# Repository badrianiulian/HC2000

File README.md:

# HC2000

## Note în limba română
Proiect de reconstrucție HC2000

Ce s-a folosit pentru a crea acest proiect:
- Versiunea originală a schemei HC-2000 Rev B care a fost obținută prin intermediul grupului Romanian Home Computer (mulțumiri speciale domnului George Chirtoacă)
- Schema Eagle a HC-2000 Rev B realizată de dl. Liviu Grama, care este de asemenea membru al grupului Romanian Home Computer
- Un exemplar fizic al unui HC-2000 Rev E furnizat de dl. Oică Cezar pentru reparații

Note despre diferențe:
- HC2000_ORIGINAL este proiectul realizat folosind scanările cablajului exemplarului fizic HC-2000 Rev E
- gerberele au fost create folosind proiectul HC2000, care este Rev E modificată pentru a include firele lipite peste cablaj
- unde se întâlnește un "-", înseamnă că acea componentă lipsește pe cablajul Rev E, dar locul de amplasare al componentei este disponibil
- pentru conectorul de alimentare am adăugat pe lângă locul de amplasare al conectorului original, un conector cu 6 pini DIN

**IMPORTANT**: În prima revizie a proiectului s-au strecurat câteva greșeli:
- Nu am observat o tăietură pe placa originală ceea ce a dus la unirea a două trasee. Această secțiune este documentată pe grupul Romanian Home Computer de Radioman V: https://groups.google.com/g/romanianhomecomputer/c/qHbKBThCIQc/m/c_SBp--mCgAJ

- Au rămas două circuite cu titulatura veche de pe proiectul original care a fost convertit:

- Portul serial a fost testat de svpantazi. Modificarea se face sub UE10:

## English notes
HC2000 rebuild project

What was used to create this project:
- Original version of the schematic of HC-2000 Rev B that was obtained through the Romanian Home Computer group (special thanks to mr. George Chirtoacă)
- Eagle schematic of the HC-2000 Rev B made by mr. Liviu Grama also a member of the Romanian Home Computer group
- A physical HC-2000 Rev E provided by mr. Oică Cezar for repairs

Notes on the diferences:
- HC2000_ORIGINAL is the project made using PCB scans of the physical HC-2000 Rev E
- gerbers were created using HC2000 project witch is the modified Rev E witch includes the over-the-PCB soldered wires
- where a "-" is encountered, it means that the component is missing on Rev E but the footprint is available
- for the power connector I added side by side with the original connector's footprint, a 6-pin DIN connector

**IMPORTANT**: In the original project a few mistakes slipped in.
- I did not notice a cut on the original PCB witch led to joining of two tracks. This section is documented on the Romanian Home Computer group by Radioman V: https://groups.google.com/g/romanianhomecomputer/c/qHbKBThCIQc/m/c_SBp--mCgAJ

- Two circuits retained the old names from the original converted project:

- The serial port was tested by svpantazi. The fix is under UE10:

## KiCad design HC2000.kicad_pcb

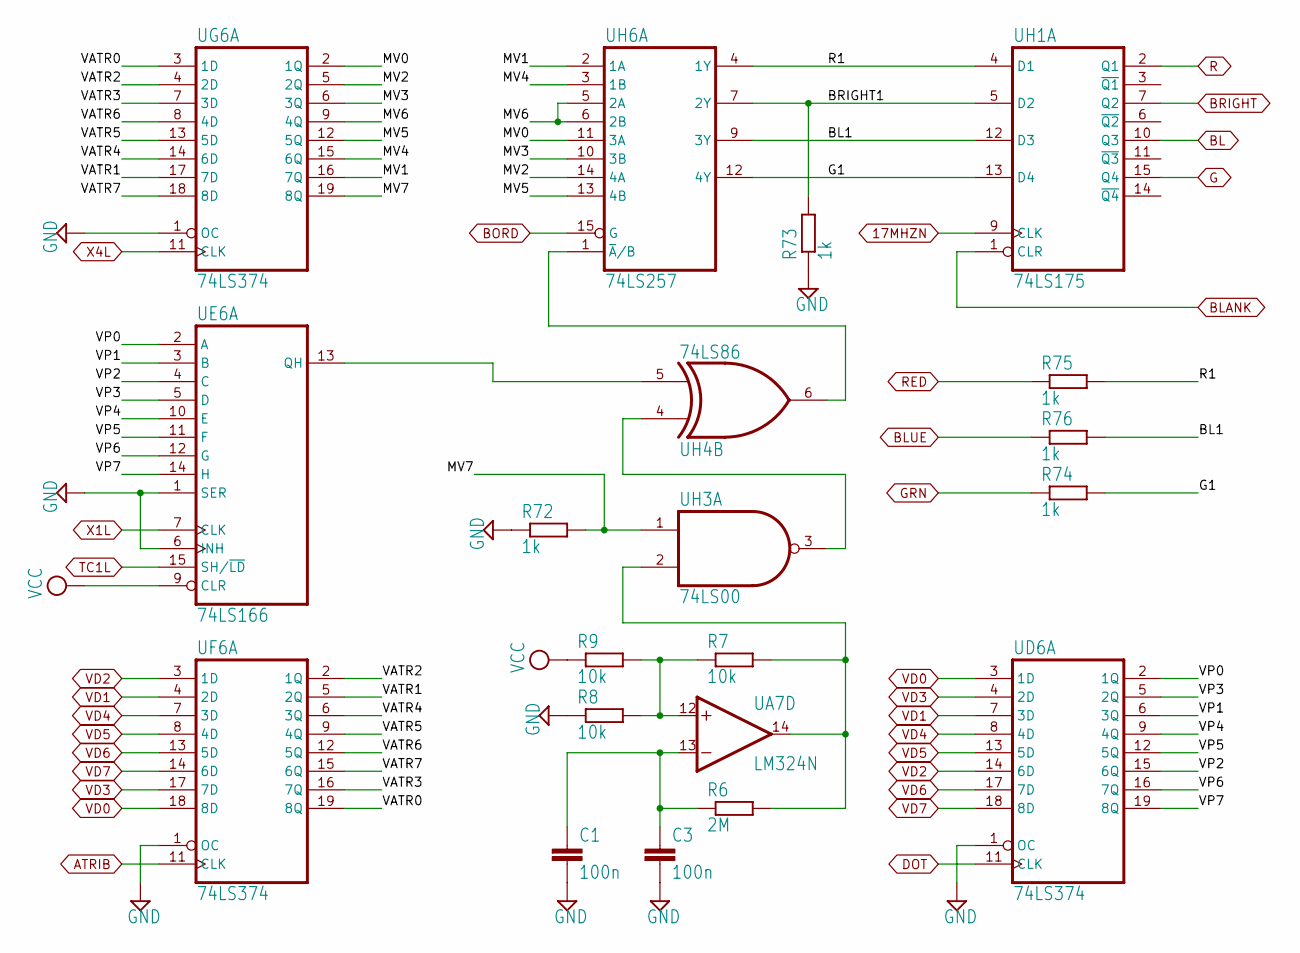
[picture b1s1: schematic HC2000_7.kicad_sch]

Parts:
C1, C3: 100n; C025-030X050
R6: 2M; 0204_7
R7, R8, R9: 10k; 0204_7
R72, R73, R74, R75, R76: 1k; 0204_7
UA7: LM324N; DIL14
UD6: 74LS374; DIL20
UE6: 74LS166; DIL16
UF6: 74LS374; DIL20
UG6: 74LS374; DIL20
UH1: 74LS175; DIL16
UH3: 74LS00; DIL14
UH4: 74LS86; DIL14
UH6: 74LS257; DIL16

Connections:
17MHZN: UH1.9 (CLK); also elsewhere on the board
/HC2000_7/BL1: R76.2, UH1.12 (D3), UH6.9 (3Y)
/HC2000_7/BRIGHT1: R73.2, UH1.5 (D2), UH6.7 (2Y)
/HC2000_7/G1: R74.2, UH1.13 (D4), UH6.12 (4Y)
/HC2000_7/MV0: UG6.2 (1Q), UH6.11 (3A)
/HC2000_7/MV1: UG6.16 (7Q), UH6.2 (1A)
/HC2000_7/MV2: UG6.5 (2Q), UH6.14 (4A)
/HC2000_7/MV3: UG6.6 (3Q), UH6.10 (3B)
/HC2000_7/MV4: UG6.15 (6Q), UH6.3 (1B)
/HC2000_7/MV5: UG6.12 (5Q), UH6.13 (4B)
/HC2000_7/MV6: UG6.9 (4Q), UH6.5 (2A), UH6.6 (2B)
/HC2000_7/MV7: R72.2, UG6.19 (8Q), UH3.1 (I0)
/HC2000_7/R1: R75.2, UH1.4 (D1), UH6.4 (1Y)
/HC2000_7/VATR0: UF6.19 (8Q), UG6.3 (1D)
/HC2000_7/VATR1: UF6.5 (2Q), UG6.17 (7D)
/HC2000_7/VATR2: UF6.2 (1Q), UG6.4 (2D)
/HC2000_7/VATR3: UF6.16 (7Q), UG6.7 (3D)
/HC2000_7/VATR4: UF6.6 (3Q), UG6.14 (6D)
/HC2000_7/VATR5: UF6.9 (4Q), UG6.13 (5D)
/HC2000_7/VATR6: UF6.12 (5Q), UG6.8 (4D)
/HC2000_7/VATR7: UF6.15 (6Q), UG6.18 (8D)
/HC2000_7/VP0: UD6.2 (1Q), UE6.2 (A)
/HC2000_7/VP1: UD6.6 (3Q), UE6.3 (B)
/HC2000_7/VP2: UD6.15 (6Q), UE6.4 (C)
/HC2000_7/VP3: UD6.5 (2Q), UE6.5 (D)
/HC2000_7/VP4: UD6.9 (4Q), UE6.10 (E)
/HC2000_7/VP5: UD6.12 (5Q), UE6.11 (F)
/HC2000_7/VP6: UD6.16 (7Q), UE6.12 (G)
/HC2000_7/VP7: UD6.19 (8Q), UE6.14 (H)
ATRIB: UF6.11 (CLK); also elsewhere on the board
BLANK: UH1.1 (CLR); also elsewhere on the board
BLUE: R76.1; also elsewhere on the board
BORD: UH6.15 (G); also elsewhere on the board
BRIGHT: UH1.7 (Q2); also elsewhere on the board
DOT: UD6.11 (CLK); also elsewhere on the board
GRN: R74.1; also elsewhere on the board
unnamed: R7.1, R8.2, R9.2, UA7.12 (+IN)
unnamed: C1.1, C3.1, R6.1, UA7.13 (-IN)
unnamed: R6.2, R7.2, UA7.14 (OUT), UH3.2 (I1)
unnamed: UE6.13 (QH), UH4.5 (I1)
unnamed: UH3.3 (O), UH4.4 (I0)
unnamed: UH4.6 (O), UH6.1 (~A/B)
RED: R75.1; also elsewhere on the board
TC1L: UE6.15 (SH/~LD); also elsewhere on the board
VD0: UD6.3 (1D), UF6.18 (8D); also elsewhere on the board
VD1: UD6.7 (3D), UF6.4 (2D); also elsewhere on the board
VD2: UD6.14 (6D), UF6.3 (1D); also elsewhere on the board
VD3: UD6.4 (2D), UF6.17 (7D); also elsewhere on the board
VD4: UD6.8 (4D), UF6.7 (3D); also elsewhere on the board
VD5: UD6.13 (5D), UF6.8 (4D); also elsewhere on the board
VD6: UD6.17 (7D), UF6.13 (5D); also elsewhere on the board
VD7: UD6.18 (8D), UF6.14 (6D); also elsewhere on the board
X1L: UE6.7 (CLK); also elsewhere on the board
X4L: UG6.11 (CLK); also elsewhere on the board

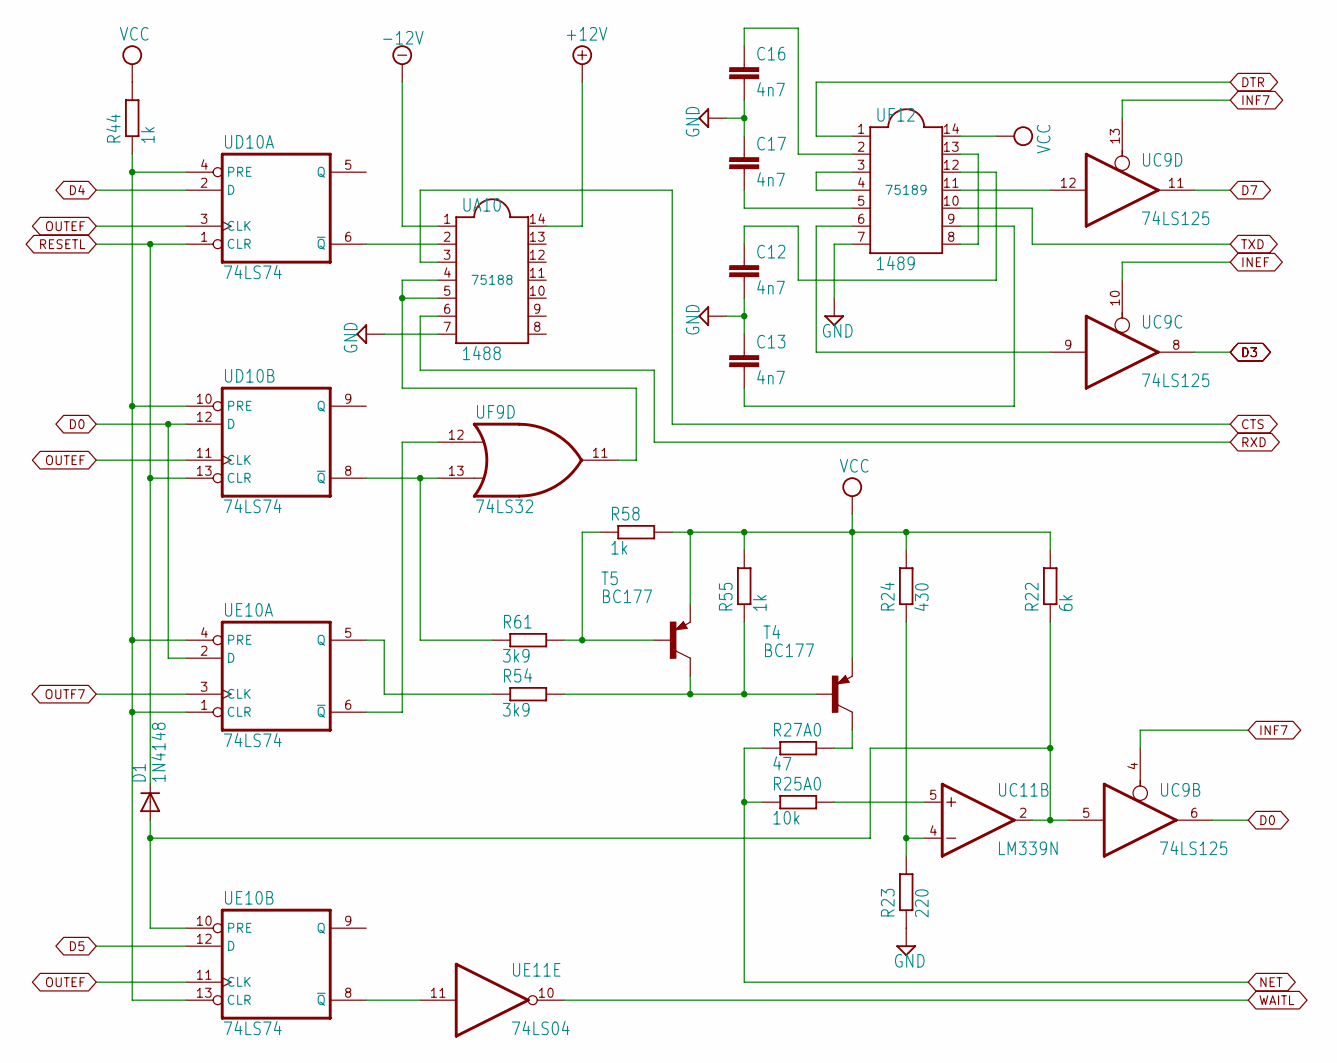
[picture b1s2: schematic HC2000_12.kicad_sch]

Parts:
C12, C13, C16, C17: 4n7; C025-025X050
D1: 1N4148; DO35-10
R22: 6k; 0204_7
R23: 220; 0204_7
R24: 430; 0204_7
R25A0: 10k; 0204_7
R27A0: 47; 0204_7
R44, R55, R58: 1k; 0204_7
R54, R61: 3k9; 0204_7
T4, T5: BC177; TO18
UA10: 1488; DIL14
UC9: 74LS125; DIL14
UC11: LM339N; DIL14
UD10: 74LS74; DIL14
UE10: 74LS74; DIL14
UE11: 74LS04; DIL14
UF9: 74LS32; DIL14
UF12: 1489; DIL14

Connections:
+12V: UA10.14; also elsewhere on the board
-12V: UA10.1; also elsewhere on the board
CTS: UA10.3; also elsewhere on the board
D4: UD10.2 (D); also elsewhere on the board
D5: UE10.12 (D); also elsewhere on the board
D7: UC9.11 (O); also elsewhere on the board
DTR: UF12.1; also elsewhere on the board
INEF: UC9.10 (OE); also elsewhere on the board
INF7: UC9.4 (OE), UC9.13 (OE); also elsewhere on the board
NET: R25A0.1, R27A0.1; also elsewhere on the board
unnamed: C12.1, UF12.12
unnamed: C13.2, UF12.9
unnamed: C16.1, UF12.2
unnamed: C17.2, UF12.5
unnamed: R54.2, R55.1, T4.2 (B), T5.3 (C)
unnamed: R27A0.2, T4.3 (C)
unnamed: R58.1, R61.2, T5.2 (B)
unnamed: UC9.9 (I), UF12.6
unnamed: UC9.12 (I), UF12.11
unnamed: R25A0.2, UC11.5 (+IN)
unnamed: R23.2, R24.1, UC11.4 (-IN)
unnamed: D1.A, R22.1, UC9.5 (I), UC11.2 (OUT), UE10.10 (PRE)
unnamed: R44.1, UD10.4 (PRE), UD10.10 (PRE), UE10.1 (CLR), UE10.4 (PRE), UE10.13 (CLR)
unnamed: UA10.2, UD10.6 (~Q)
unnamed: R61.1, UD10.8 (~Q), UF9.13 (I1)
unnamed: R54.1, UE10.5 (Q)
unnamed: UE10.6 (~Q), UF9.12 (I0)
unnamed: UE10.8 (~Q), UE11.11 (I)
unnamed: UA10.4, UA10.5, UF9.11 (O)
unnamed: UF12.3, UF12.4
unnamed: UF12.8, UF12.13
OUTEF: UD10.3 (CLK), UD10.11 (CLK), UE10.11 (CLK); also elsewhere on the board
OUTF7: UE10.3 (CLK); also elsewhere on the board
RESETL: D1.C, UD10.1 (CLR), UD10.13 (CLR); also elsewhere on the board
RXD: UA10.6; also elsewhere on the board
TXD: UF12.10; also elsewhere on the board
WAITL: UE11.10 (O); also elsewhere on the board

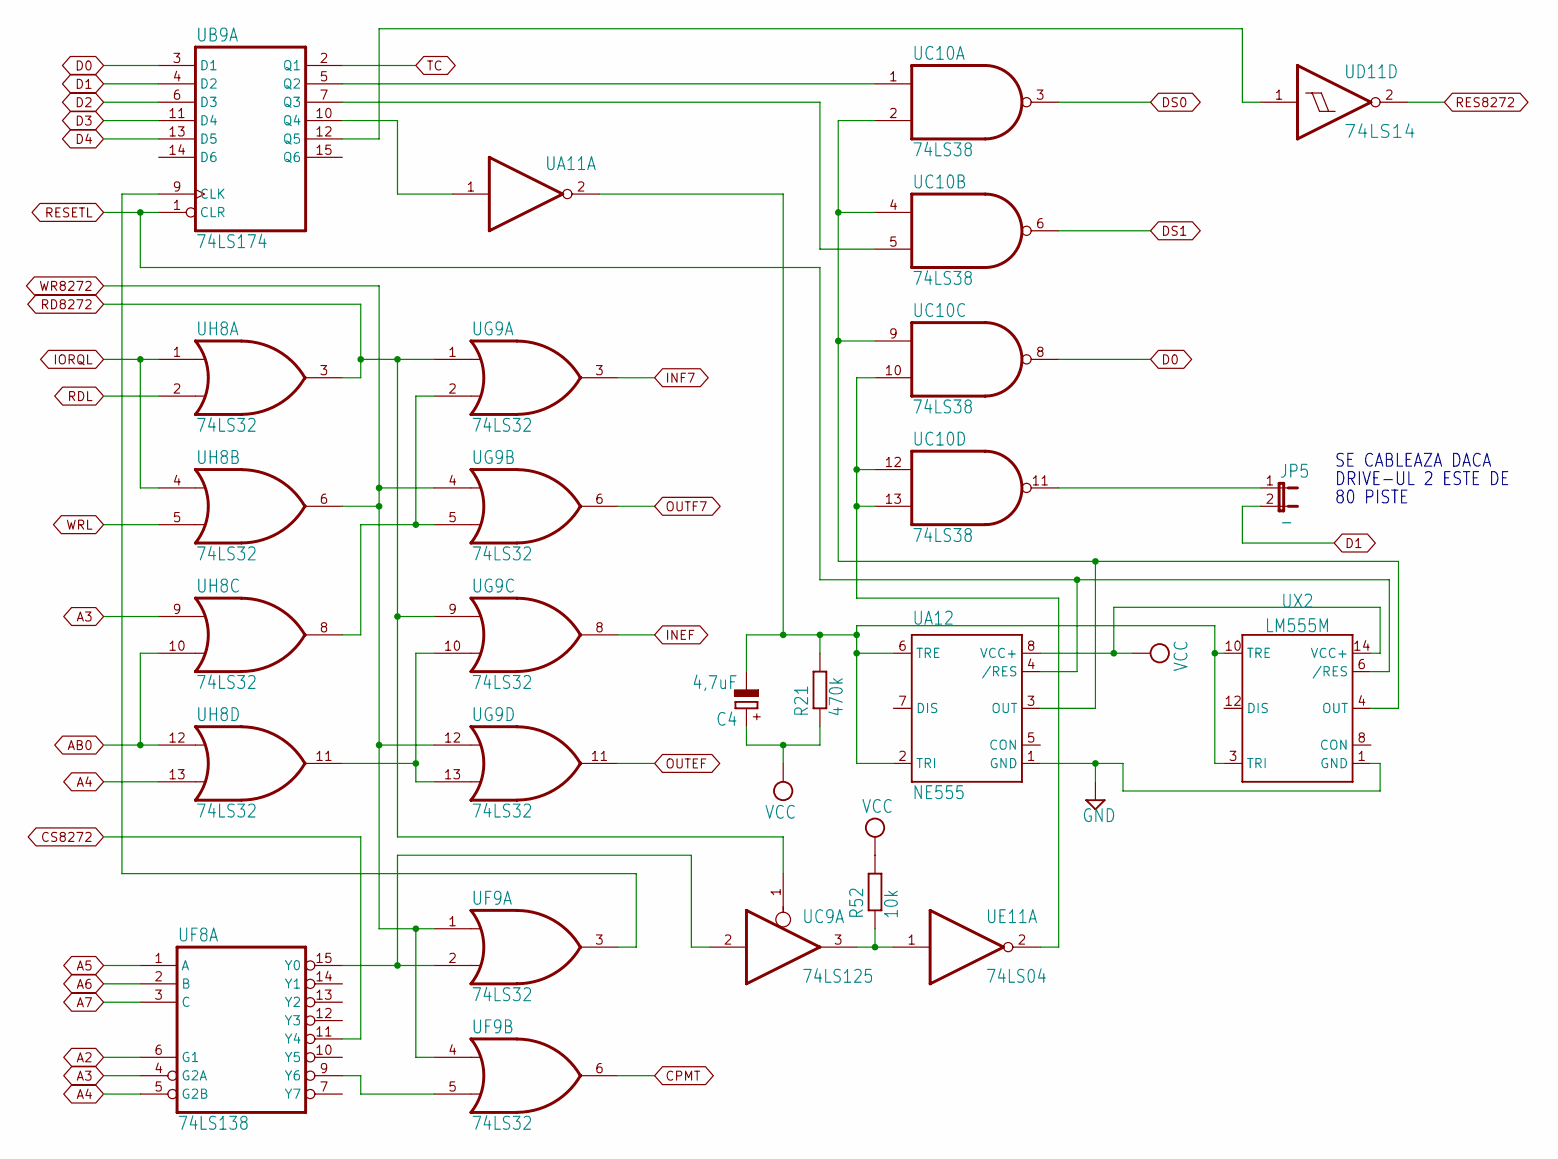
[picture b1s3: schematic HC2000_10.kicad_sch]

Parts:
C4: 4,7uF; C025-024X044
JP5: -; JP1
R21: 470k; 0204_7
R52: 10k; 0204_7
UA11: 74LS06; DIL14
UA12: NE555; DIL-08
UB9: 74LS174; DIL16
UC9: 74LS125; DIL14
UC10: 74LS38; DIL14
UD11: 74LS14; DIL14
UE11: 74LS04; DIL14
UF8: 74LS138; DIL16
UF9: 74LS32; DIL14
UG9: 74LS32; DIL14
UH8: 74LS32; DIL14
UX2: LM555M; DIL14

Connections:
AB0: UH8.10 (I1), UH8.12 (I0); also elsewhere on the board
CPMT: UF9.6 (O); also elsewhere on the board
CS8272: UF8.11 (Y4); also elsewhere on the board
D4: UB9.13 (D5); also elsewhere on the board
DS0: UC10.3 (O); also elsewhere on the board
DS1: UC10.6 (O); also elsewhere on the board
INEF: UG9.8 (O); also elsewhere on the board
INF7: UG9.3 (O); also elsewhere on the board
IORQL: UH8.1 (I0), UH8.4 (I0); also elsewhere on the board
unnamed: UA11.1 (I), UB9.10 (Q4)
unnamed: C4.-, R21.2, UA11.2 (O), UA12.2 (TRI), UA12.6 (TRE), UX2.3 (TRI), UX2.10 (TRE)
unnamed: UA12.3 (OUT), UC10.2 (I1), UC10.4 (I0), UC10.9 (I0), UX2.4 (OUT)
unnamed: UB9.9 (CLK), UF9.3 (O)
unnamed: UB9.5 (Q2), UC10.1 (I0)
unnamed: UB9.7 (Q3), UC10.5 (I1)
unnamed: UB9.12 (Q5), UD11.1 (I)
unnamed: UC9.2 (I), UF8.15 (Y0), UF9.2 (I1)
unnamed: R52.1, UC9.3 (O), UE11.1 (I)
unnamed: UC10.10 (I1), UC10.12 (I0), UC10.13 (I1), UE11.2 (O)
unnamed: JP5.1, UC10.11 (O)
unnamed: UF8.9 (Y6), UF9.5 (I1)
unnamed: UG9.2 (I1), UG9.5 (I1), UH8.8 (O)
unnamed: UG9.10 (I1), UG9.13 (I1), UH8.11 (O)
OUTEF: UG9.11 (O); also elsewhere on the board
OUTF7: UG9.6 (O); also elsewhere on the board
RD8272: UC9.1 (OE), UG9.1 (I0), UG9.9 (I0), UH8.3 (O); also elsewhere on the board
RDL: UH8.2 (I1); also elsewhere on the board
RES8272: UD11.2 (O); also elsewhere on the board
RESETL: UA12.4 (/RES), UB9.1 (CLR), UX2.6 (/RES); also elsewhere on the board
TC: UB9.2 (Q1); also elsewhere on the board
WR8272: UF9.1 (I0), UF9.4 (I0), UG9.4 (I0), UG9.12 (I0), UH8.6 (O); also elsewhere on the board
WRL: UH8.5 (I1); also elsewhere on the board

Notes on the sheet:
80 PISTE
SE CABLEAZA DACA
DRIVE-UL 2 ESTE DE

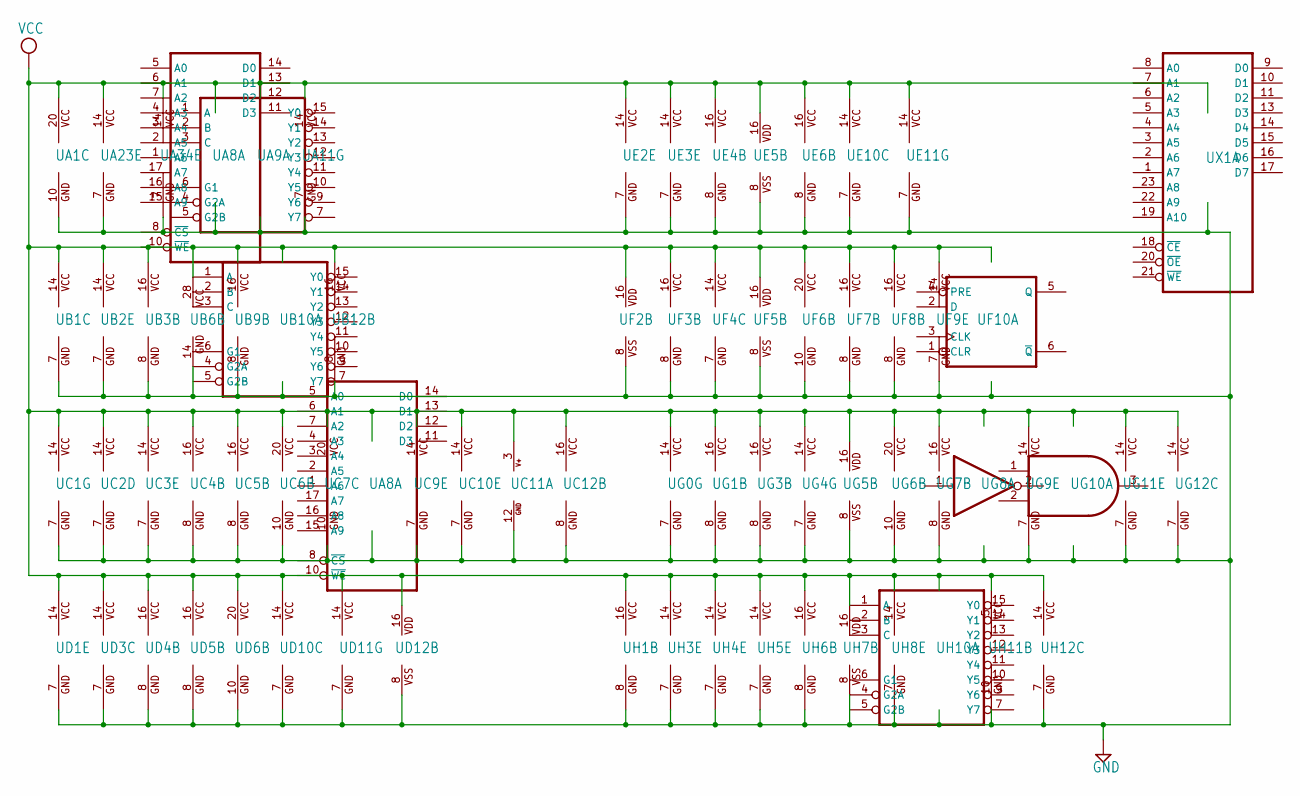
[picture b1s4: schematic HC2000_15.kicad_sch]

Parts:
UA1: 74LS244; DIL20
UA8: -; DIL18
UA9: 74LS138; DIL16
UA11: 74LS06; DIL14
UA23, UA34: 74LS09; DIL14
UB1: 74LS74; DIL14
UB2: 74LS00; DIL14
UB3: 74LS367; DIL16
UB6: 27C512; DIL28
UB9: 74LS174; DIL16
UB10: 74LS138; DIL16
UB12: 74LS153; DIL16
UC1: 74LS04; DIL14
UC2: 74LS27; DIL14
UC3: 74LS32; DIL14
UC4, UC5: 74LS257; DIL16
UC6: 74LS373; DIL20
UC7: 74LS244; DIL20
UC9: 74LS125; DIL14
UC10: 74LS38; DIL14
UC11: LM339N; DIL14
UC12: 74LS175; DIL16
UD1: 74LS08; DIL14
UD3, UD10: 74LS74; DIL14
UD4: 74LS157; DIL16
UD5: 74LS257; DIL16
UD6: 74LS374; DIL20
UD11: 74LS14; DIL14
UD12: 74LS161; DIL16
UE2: 74LS08; DIL14
UE3: 74LS32; DIL14
UE4: 74LS138; DIL16
UE5: 74LS161; DIL16
UE6: 74LS166; DIL16
UE10: 74LS74; DIL14
UE11: 74LS04; DIL14
UF2, UF5: 74LS161; DIL16
UF3: 74LS175; DIL16
UF4, UF10: 74LS74; DIL14
UF6: 74LS374; DIL20
UF7: 74LS174; DIL16
UF8: 74LS138; DIL16
UF9: 74LS32; DIL14
UG0, UG4: 74LS04; DIL14
UG1: 74LS42; DIL16
UG3: 74LS175; DIL16
UG5: 74LS161; DIL16
UG6: 74LS374; DIL20
UG7: 74LS257; DIL16
UG8: 74LS05; DIL14
UG9: 74LS32; DIL14
UG10, UG11: 74LS08; DIL14
UG12: 74LS74; DIL14
UH1: 74LS175; DIL16
UH3: 74LS00; DIL14
UH4: 74LS86; DIL14
UH5: 74LS08; DIL14
UH6: 74LS257; DIL16
UH7: 74LS161; DIL16
UH8: 74LS32; DIL14
UH10: 74LS138; DIL16
UH11: 74LS93; DIL14
UH12: 74LS74; DIL14
UX1: UM6116-3; DIL24

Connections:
/HC2000_11/PHANTOM: UB10.6 (G1), UF10.5 (Q); also elsewhere on the board
A15: UB10.5 (G2B); also elsewhere on the board
D4: UA8.14 (D0), UX1.14 (D4); also elsewhere on the board
D5: UA8.13 (D1), UX1.15 (D5); also elsewhere on the board
D6: UA8.12 (D2), UX1.16 (D6); also elsewhere on the board
D7: UA8.11 (D3), UX1.17 (D7); also elsewhere on the board
M1L: UA9.4 (G2A); also elsewhere on the board
unnamed 154: UA9.6 (G1), UG8.2 (O); also elsewhere on the board
unnamed 155: UA9.5 (G2B); also elsewhere on the board
unnamed 156: UA9.15 (Y0), UH10.2 (B); also elsewhere on the board
unnamed 157: UA9.7 (Y7); also elsewhere on the board
unnamed 178: UB10.15 (Y0); also elsewhere on the board
unnamed: UF10.3 (CLK), UH10.13 (Y2)
unnamed 242: UF10.4 (PRE); also elsewhere on the board
unnamed 258: UH10.6 (G1); also elsewhere on the board
unnamed 259: UH10.14 (Y1); also elsewhere on the board
unnamed 260: UH10.7 (Y7); also elsewhere on the board
RESETL: UF10.1 (CLR); also elsewhere on the board
WRL: UA8.10 (~WE), UX1.21 (~WE); also elsewhere on the board

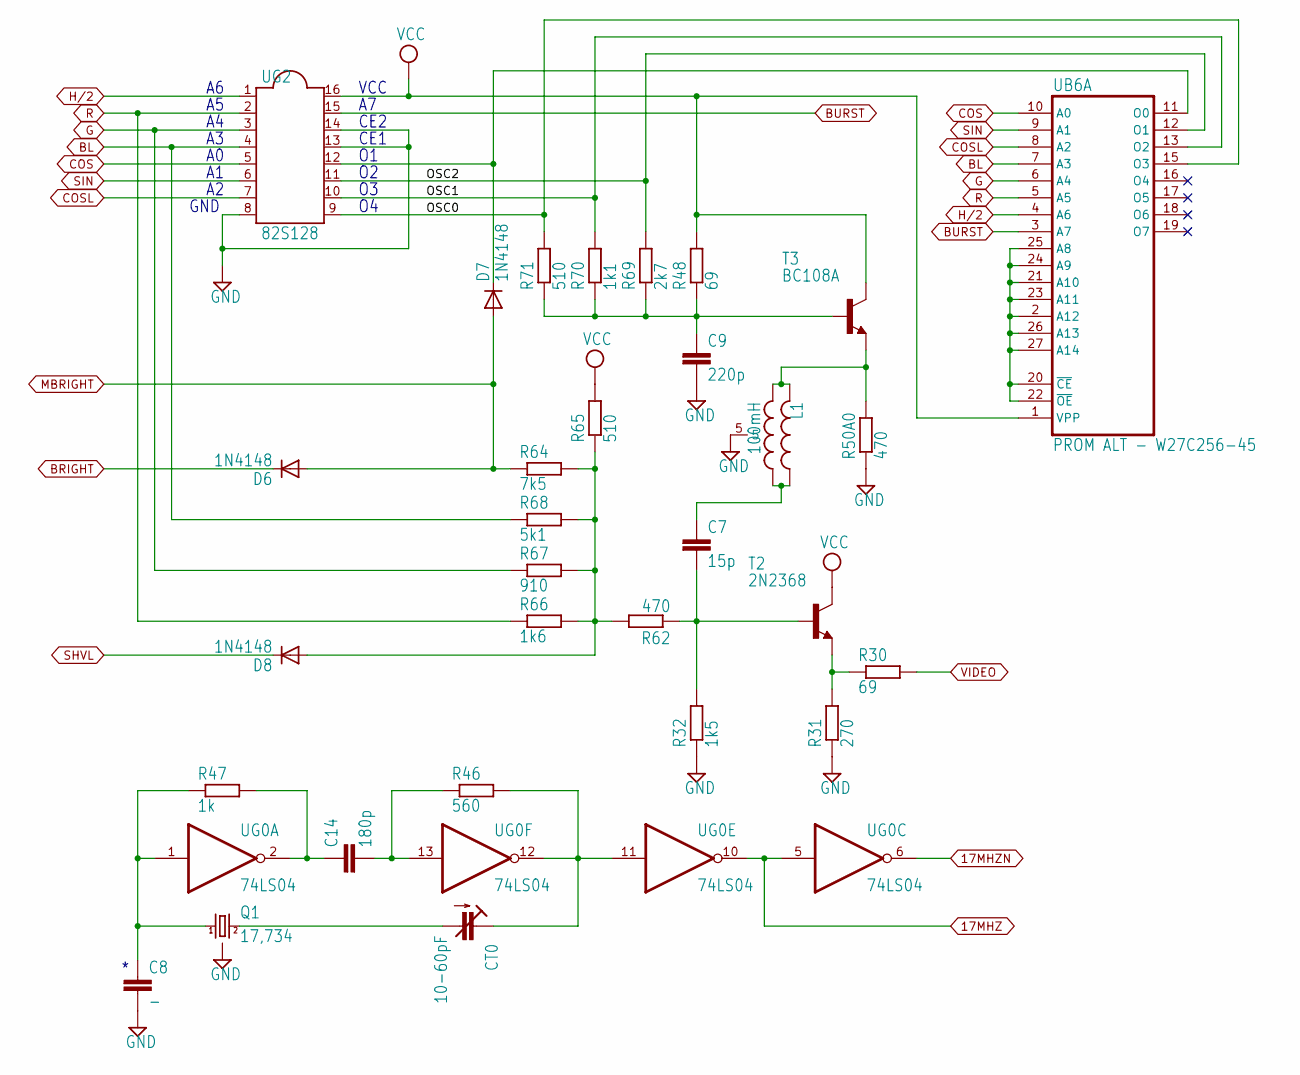
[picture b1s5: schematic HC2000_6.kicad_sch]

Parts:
C7: 15p; C025-030X050
C8: -; C025-030X050
C9: 220p; C025-030X050
C14: 180p; C025-030X050
CT0: 10-60pF; CTRIM808-BC
D6, D7, D8: 1N4148; DO35-10
L1: 100mH; PIS2816
Q1: 17,734; HC18U-H
R30, R48: 69; 0204_7
R31: 270; 0204_7
R32: 1k5; 0204_7
R46: 560; 0204_7
R47: 1k; 0204_7
R50A0, R62: 470; 0204_7
R64: 7k5; 0204_7
R65, R71: 510; 0204_7
R66: 1k6; 0204_7
R67: 910; 0204_7
R68: 5k1; 0204_7
R69: 2k7; 0204_7
R70: 1k1; 0204_7
T2: 2N2368; TO18
T3: BC108A; TO18
UB6: PROM ALT - W27C256-45; DIL28
UG0: 74LS04; DIL14
UG2: 82S128; DIL16

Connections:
17MHZ: UG0.5 (I), UG0.10 (O); also elsewhere on the board
17MHZN: UG0.6 (O); also elsewhere on the board
BRIGHT: D6.C; also elsewhere on the board
D4: UB6.16 (O4); also elsewhere on the board
D5: UB6.17 (O5); also elsewhere on the board
D6: UB6.18 (O6); also elsewhere on the board
D7: UB6.19 (O7); also elsewhere on the board
MBRIGHT: D6.A, D7.A, R64.1; also elsewhere on the board
unnamed: C7.1, L1.1, L1.4
unnamed: CT0.2 (A), Q1.2
unnamed: D8.A, R62.2, R64.2, R65.1, R66.2, R67.2, R68.2
unnamed: C7.2, R32.2, R62.1, T2.2 (B)
unnamed: R30.1, R31.2, T2.1 (E)
unnamed: C9.1, R48.1, R69.1, R70.1, R71.1, T3.2 (B)
unnamed: L1.2, L1.3, R50A0.2, T3.1 (E)
unnamed: C8.1, Q1.1, R47.1, UG0.1 (I)
unnamed: C14.1, R47.2, UG0.2 (O)
unnamed: CT0.1 (E), CT0.3 (E), R46.2, UG0.11 (I), UG0.12 (O)
unnamed: C14.2, R46.1, UG0.13 (I)
SHVL: D8.C; also elsewhere on the board
VIDEO: R30.2; also elsewhere on the board

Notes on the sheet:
VCC
CE2
GND
CE1

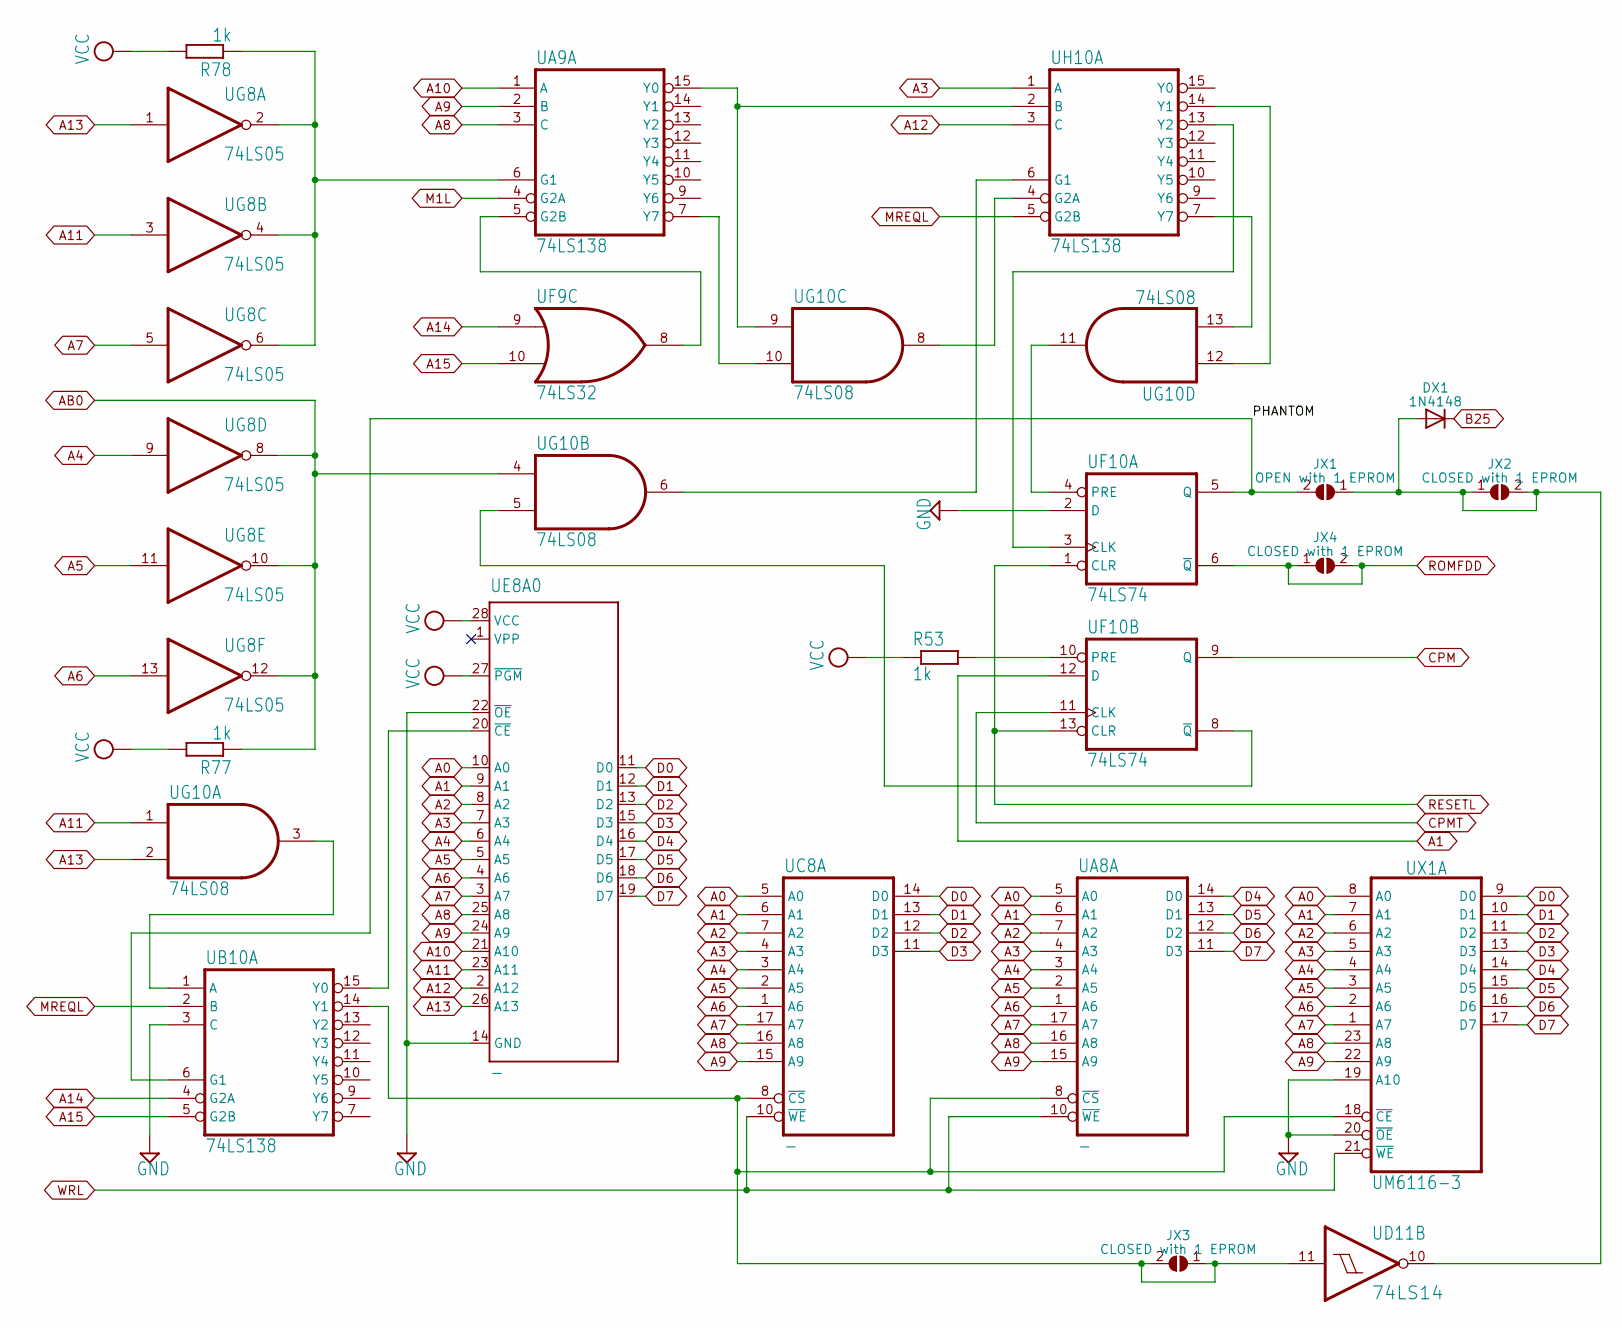
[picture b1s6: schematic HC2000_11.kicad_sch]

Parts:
DX1: 1N4148; DO35-7
JX1: OPEN with 1 EPROM; SolderJumper-2_P1.3mm_Open_Pad1.0x1.5mm
JX2, JX3, JX4: CLOSED with 1 EPROM; SolderJumper-2_P1.3mm_Open_Pad1.0x1.5mm
R53, R77, R78: 1k; 0204_7
UA8: -; DIL18
UA9: 74LS138; DIL16
UB10: 74LS138; DIL16
UC8: -; DIL18
UD11: 74LS14; DIL14
UE8A0: -; DIL28-6
UF9: 74LS32; DIL14
UF10: 74LS74; DIL14
UG8: 74LS05; DIL14
UG10: 74LS08; DIL14
UH10: 74LS138; DIL16
UX1: UM6116-3; DIL24

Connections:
/HC2000_11/PHANTOM: JX1.2 (B), UB10.6 (G1), UF10.5 (Q)
A15: UB10.5 (G2B), UF9.10 (I1); also elsewhere on the board
AB0: R77.1, UG8.8 (O), UG8.10 (O), UG8.12 (O), UG10.4 (I0); also elsewhere on the board
B25: DX1.C; also elsewhere on the board
CPM: UF10.9 (Q); also elsewhere on the board
CPMT: UF10.11 (CLK); also elsewhere on the board
D4: UA8.14 (D0), UE8A0.16 (D4), UX1.14 (D4); also elsewhere on the board
D5: UA8.13 (D1), UE8A0.17 (D5), UX1.15 (D5); also elsewhere on the board
D6: UA8.12 (D2), UE8A0.18 (D6), UX1.16 (D6); also elsewhere on the board
D7: UA8.11 (D3), UE8A0.19 (D7), UX1.17 (D7); also elsewhere on the board
M1L: UA9.4 (G2A); also elsewhere on the board
unnamed: R78.1, UA9.6 (G1), UG8.2 (O), UG8.4 (O), UG8.6 (O)
unnamed: UA9.5 (G2B), UF9.8 (O)
unnamed: UA9.15 (Y0), UG10.9 (I0), UH10.2 (B)
unnamed: UA9.7 (Y7), UG10.10 (I1)
unnamed: UB10.15 (Y0), UE8A0.20 (~CE)
unnamed: UF10.3 (CLK), UH10.13 (Y2)
unnamed: UF10.4 (PRE), UG10.11 (O)
unnamed: R53.2, UF10.10 (PRE)
unnamed: UF10.8 (~Q), UG10.5 (I1)
unnamed: UG10.6 (O), UH10.6 (G1)
unnamed: UG10.12 (I0), UH10.14 (Y1)
unnamed: UG10.13 (I1), UH10.7 (Y7)
RESETL: UF10.1 (CLR), UF10.13 (CLR); also elsewhere on the board
WRL: UA8.10 (~WE), UC8.10 (~WE), UX1.21 (~WE); also elsewhere on the board

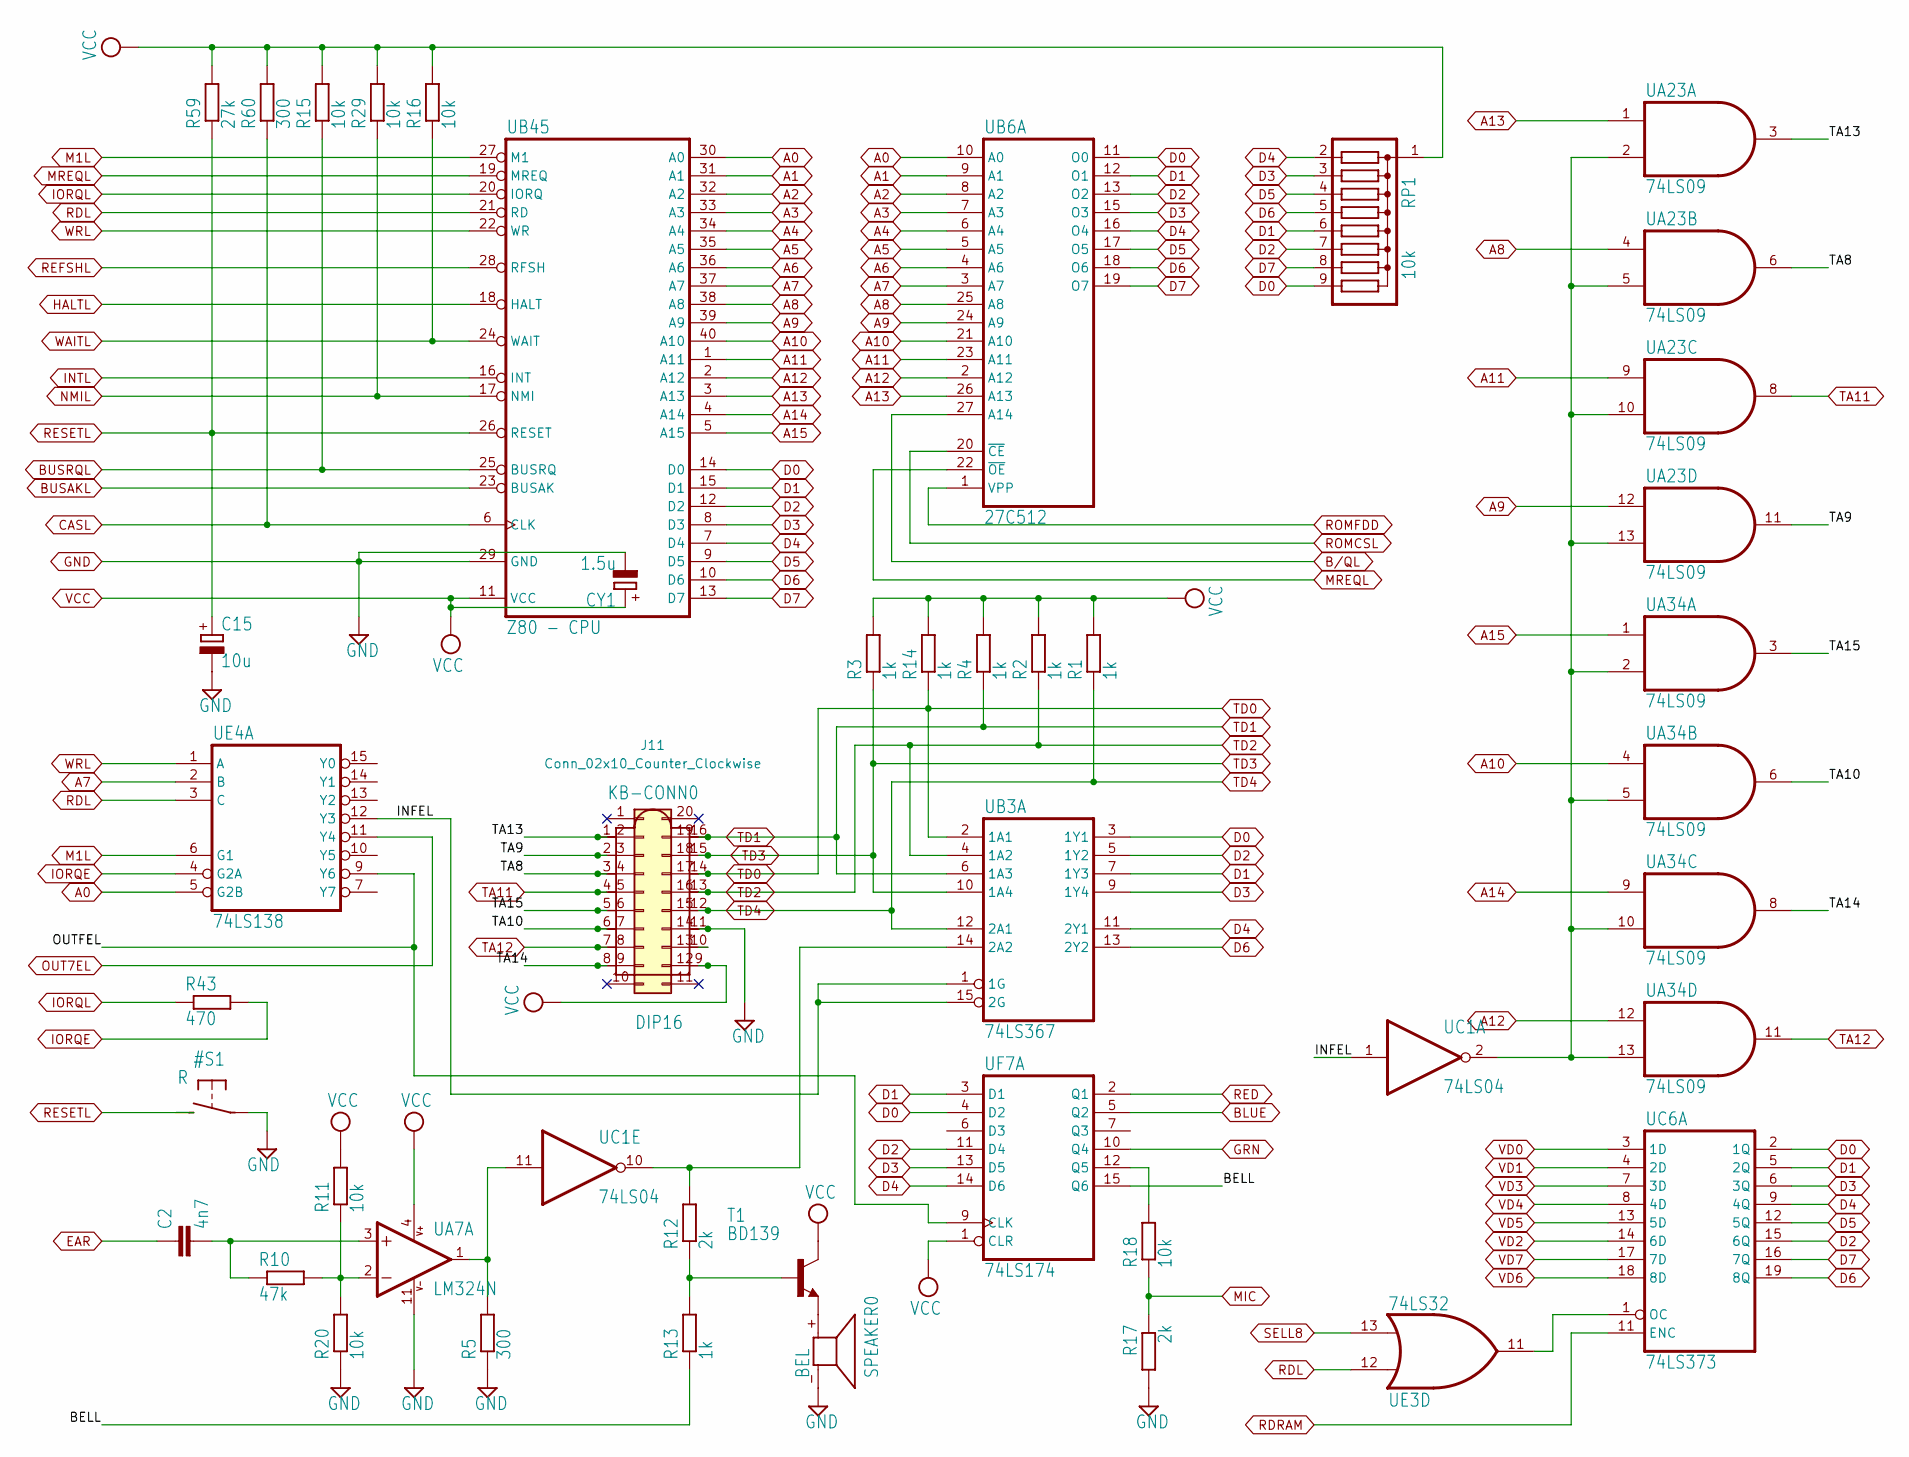
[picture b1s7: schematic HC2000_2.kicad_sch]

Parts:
C2: 4n7; C025-030X050
C15: 10u; C025-024X024
CY1: 1.5u
J11: Conn_02x10_Counter_Clockwise; PinHeader_2x10_P2.54mm_Vertical
KB-CONN0: DIP16; DIL16
R1, R2, R3, R4, R13, R14: 1k; 0204_7
R5, R60: 300; 0204_7
R10: 47k; 0204_7
R11, R15, R16, R18, R20, R29: 10k; 0204_7
R12, R17: 2k; 0204_7
R43: 470; 0204_7
R59: 27k; 0204_7
RP1: 10k; SIL9
SPEAKER0: BEL; AL11P
T1: BD139; TO-126-3_Vertical
UA7: LM324N; DIL14
UA23, UA34: 74LS09; DIL14
UB3: 74LS367; DIL16
UB6: 27C512; DIL28
UB45: Z80 - CPU; DIL40
UC1: 74LS04; DIL14
UC6: 74LS373; DIL20
UE3: 74LS32; DIL14
UE4: 74LS138; DIL16
UF7: 74LS174; DIL16

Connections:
/HC2000_2/BELL: R13.1, UF7.15 (Q6)
/HC2000_2/INFEL: UB3.1 (1G), UB3.15 (2G), UC1.1 (I), UE4.12 (Y3)
/HC2000_2/OUTFEL: UE4.9 (Y6), UF7.9 (CLK)
/HC2000_2/TA8: J11.4, KB-CONN0.3, UA23.6 (O)
/HC2000_2/TA9: J11.3, KB-CONN0.2, UA23.11 (O)
/HC2000_2/TA10: J11.7, KB-CONN0.6, UA34.6 (O)
/HC2000_2/TA13: J11.2, KB-CONN0.1, UA23.3 (O)
/HC2000_2/TA14: J11.9, KB-CONN0.8, UA34.8 (O)
/HC2000_2/TA15: J11.6, KB-CONN0.5, UA34.3 (O)
A15: UA34.1 (I0), UB45.5 (A15); also elsewhere on the board
BLUE: UF7.5 (Q2); also elsewhere on the board
BUSAKL: UB45.23 (BUSAK); also elsewhere on the board
BUSRQL: R15.1, UB45.25 (BUSRQ); also elsewhere on the board
CASL: R60.1, UB45.6 (CLK); also elsewhere on the board
D4: RP1.2, UB3.11 (2Y1), UB6.16 (O4), UB45.7 (D4), UC6.9 (4Q), UF7.14 (D6); also elsewhere on the board
D5: RP1.4, UB6.17 (O5), UB45.9 (D5), UC6.12 (5Q); also elsewhere on the board
D6: RP1.5, UB3.13 (2Y2), UB6.18 (O6), UB45.10 (D6), UC6.19 (8Q); also elsewhere on the board
D7: RP1.8, UB6.19 (O7), UB45.13 (D7), UC6.16 (7Q); also elsewhere on the board
EAR: C2.1; also elsewhere on the board
GRN: UF7.10 (Q4); also elsewhere on the board
HALTL: UB45.18 (HALT); also elsewhere on the board
INTL: UB45.16 (INT); also elsewhere on the board
IORQE: R43.2, UE4.4 (G2A); also elsewhere on the board
IORQL: R43.1, UB45.20 (IORQ); also elsewhere on the board
M1L: UB45.27 (M1), UE4.6 (G1); also elsewhere on the board
MIC: R17.1, R18.1; also elsewhere on the board
NMIL: R29.1, UB45.17 (NMI); also elsewhere on the board
unnamed: J11.13, KB-CONN0.10
unnamed: SPEAKER0.+ (2), T1.1 (E)
unnamed: R12.1, R13.2, T1.3 (B)
unnamed: C2.2, R10.1, UA7.3 (+IN)
unnamed: R10.2, R11.1, R20.2, UA7.2 (-IN)
unnamed: R5.2, UA7.1 (OUT), UC1.11 (I)
unnamed: UA23.2 (I1), UA23.5 (I1), UA23.10 (I1), UA23.13 (I1), UA34.2 (I1), UA34.5 (I1), UA34.10 (I1), UA34.13 (I1), UC1.2 (O)
unnamed: R12.2, UB3.14 (2A2), UC1.10 (O)
unnamed: UC6.1 (OC), UE3.11 (O)
unnamed: R18.2, UF7.12 (Q5)
OUT7EL: UE4.11 (Y4); also elsewhere on the board
RDL: UB45.21 (RD), UE3.12 (I0), UE4.3 (C); also elsewhere on the board
RDRAM: UC6.11 (ENC); also elsewhere on the board
RED: UF7.2 (Q1); also elsewhere on the board
REFSHL: UB45.28 (RFSH); also elsewhere on the board
RESETL: C15.+, R59.1, UB45.26 (RESET); also elsewhere on the board
SELL8: UE3.13 (I1); also elsewhere on the board
TA11: J11.5, KB-CONN0.4, UA23.8 (O); also elsewhere on the board
TA12: J11.8, KB-CONN0.7, UA34.11 (O); also elsewhere on the board
TD0: J11.17, KB-CONN0.14, R14.1, UB3.2 (1A1); also elsewhere on the board
TD1: J11.19, KB-CONN0.16, R4.1, UB3.6 (1A3); also elsewhere on the board
TD2: J11.16, KB-CONN0.13, R2.1, UB3.4 (1A2); also elsewhere on the board
TD3: J11.18, KB-CONN0.15, R3.1, UB3.10 (1A4); also elsewhere on the board
TD4: J11.15, KB-CONN0.12, R1.1, UB3.12 (2A1); also elsewhere on the board
VD0: UC6.3 (1D); also elsewhere on the board
VD1: UC6.4 (2D); also elsewhere on the board
VD2: UC6.14 (6D); also elsewhere on the board
VD3: UC6.7 (3D); also elsewhere on the board
VD4: UC6.8 (4D); also elsewhere on the board
VD5: UC6.13 (5D); also elsewhere on the board
VD6: UC6.18 (8D); also elsewhere on the board
VD7: UC6.17 (7D); also elsewhere on the board
WAITL: R16.1, UB45.24 (WAIT); also elsewhere on the board
WRL: UB45.22 (WR), UE4.1 (A); also elsewhere on the board
